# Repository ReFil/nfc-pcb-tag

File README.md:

# nfc-pcb-tag
 NFC keychain/collar tag

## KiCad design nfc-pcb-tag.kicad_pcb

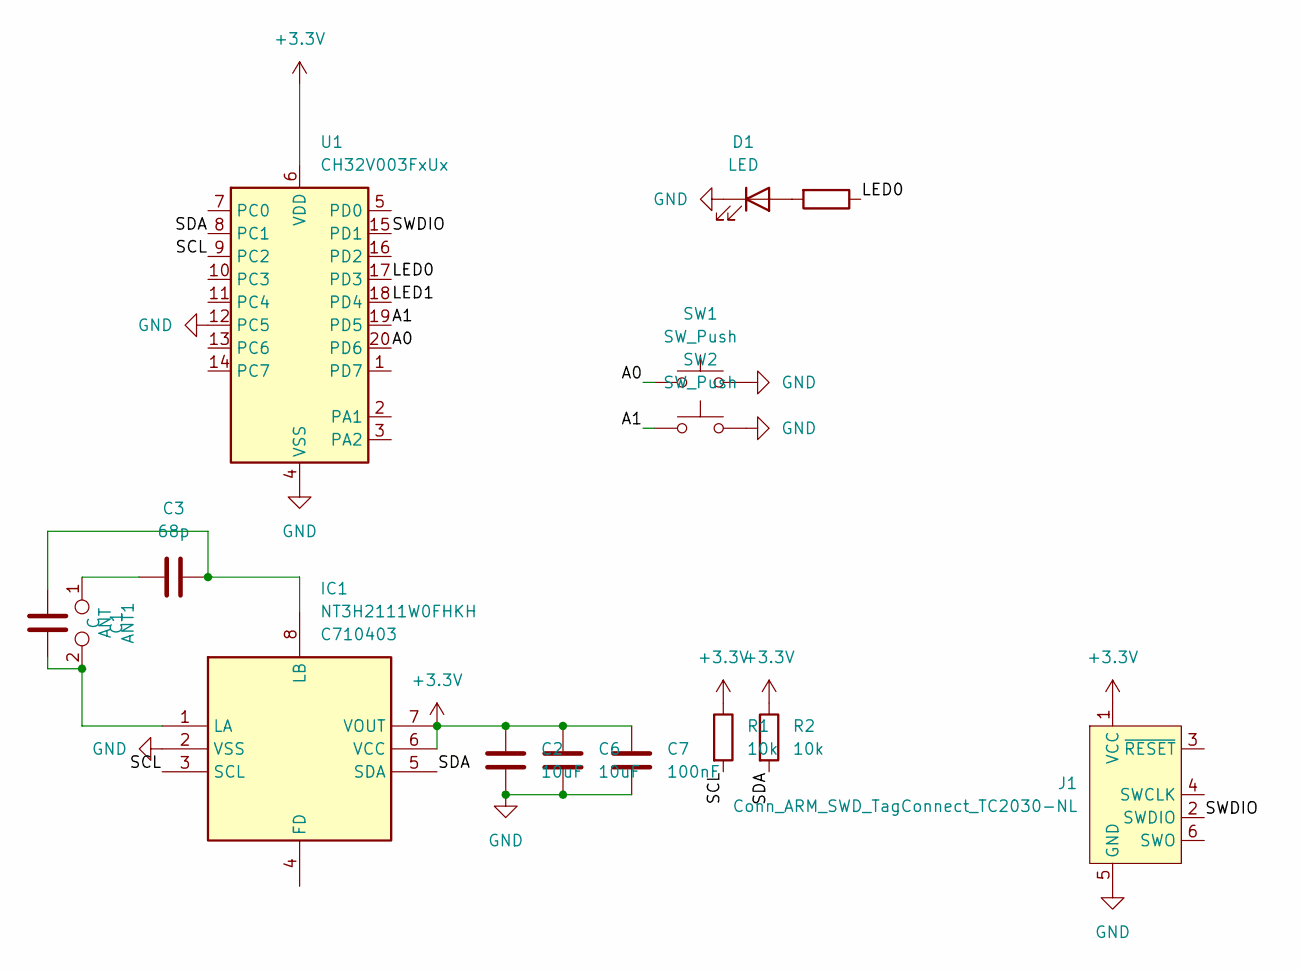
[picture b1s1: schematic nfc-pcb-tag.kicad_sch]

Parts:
ANT1: ANT; LCSC Part C33126958
C1: C; C_0402_1005Metric
C2, C6: 10uF; C_0402_1005Metric; LCSC Part C15525
C3: 68p; C_0402_1005Metric; LCSC Part C107010
C7: 100nF; C_0402_1005Metric; LCSC Part C541406
D1: LED; LED_0402_1005Metric; LCSC Part C5336761
IC1: NT3H2111W0FHKH; QFN50P160X160X50-8N; Mouser Part Number 771-NT3H2111W0FHKH
J1: Conn_ARM_SWD_TagConnect_TC2030-NL; Tag-Connect_TC2030-IDC-NL_2x03_P1.27mm_Vertical
R1, R2: 10k; R_0402_1005Metric; LCSC Part C60490
R5: 1k; R_0402_1005Metric; LCSC Part C114759
SW1, SW2: SW_Push; SW_SPST_B3U-3000P; LCSC Part C963349
U1: CH32V003FxUx; QFN-20-1EP_3x3mm_P0.4mm_EP1.65x1.65mm; LCSC Part C5299908

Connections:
+3.3V: C2.1, C6.1, C7.1, IC1.6 (VCC), IC1.7 (VOUT), J1.1 (VCC), R1.1, R2.1, U1.6 (VDD)
/A0: SW1.1, U1.20 (PD6)
/A1: SW2.1, U1.19 (PD5)
/LED0: R5.1, U1.17 (PD3)
/LED1: U1.18 (PD4)
/SCL: IC1.3 (SCL), R1.2, U1.9 (PC2)
/SDA: IC1.5 (SDA), R2.2, U1.8 (PC1)
/SWDIO: J1.2 (SWDIO), U1.15 (PD1)
GND: C2.2, C6.2, C7.2, D1.1 (K), IC1.2 (VSS), J1.5 (GND), SW1.2, SW2.2, U1.4 (VSS), U1.12 (PC5), U1.21 (VSS)
unnamed: ANT1.1, C3.1
unnamed: D1.2 (A), R5.2
unnamed: ANT1.2, C1.2, IC1.1 (LA)
unnamed: C1.1, C3.2, IC1.8 (LB)

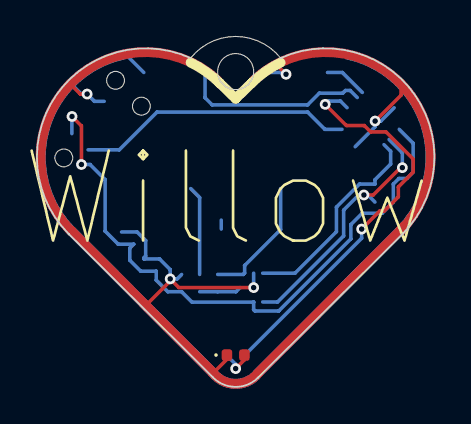
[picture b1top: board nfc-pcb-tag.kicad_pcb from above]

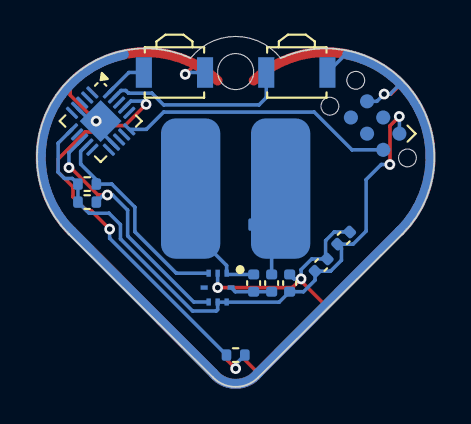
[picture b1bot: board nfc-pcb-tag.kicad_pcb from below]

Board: 2 copper layers, 22.1 x 19.4 mm, 15 parts (14 on the bottom side), 12 nets.

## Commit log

2025-02-28 Commit Firmware
2025-04-28 Tweak firmware
2025-06-11 Convert to inductor antenna
2025-06-12 Add kibot yaml
2025-06-12 Run kiibot
2025-10-06 Final gerbers and firmware tweaks
2026-01-11 Revise to use buttons
